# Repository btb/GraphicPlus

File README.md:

# GraphicPlus

Parallel printer card for Apple II

A clone of Orange Micro's Grappler+ printer card, from their published schematic, with the known bugfixes of their later revisions applied.

Component values not specified on the original schematic:

* C2, C4, C5, C5 - bypass capactors, 100nF should be fine.
* C1, C3, C7, C8 - on photos I've seen, C1 is 100pF, C3 is 470pF, C7 is 100pF. 100p for C8 should be fine as well.
* D1 - signal diode, 1n4148, 1n914, etc should be fine.

If you only want to use this as a firmware expansion card (i.e. for SoftSP), you can omit U5, U6, U10, U11, S1, D1, and J2.

Pins 2,4,6,8 of the port header are left unconnected for maximum compatibility with common PC parallel port IDC26F to DB25F dongles. If you need those pins to be connected to ground as in the original Grappler cards, short jumpers JP1,JP2,JP3,JP4.

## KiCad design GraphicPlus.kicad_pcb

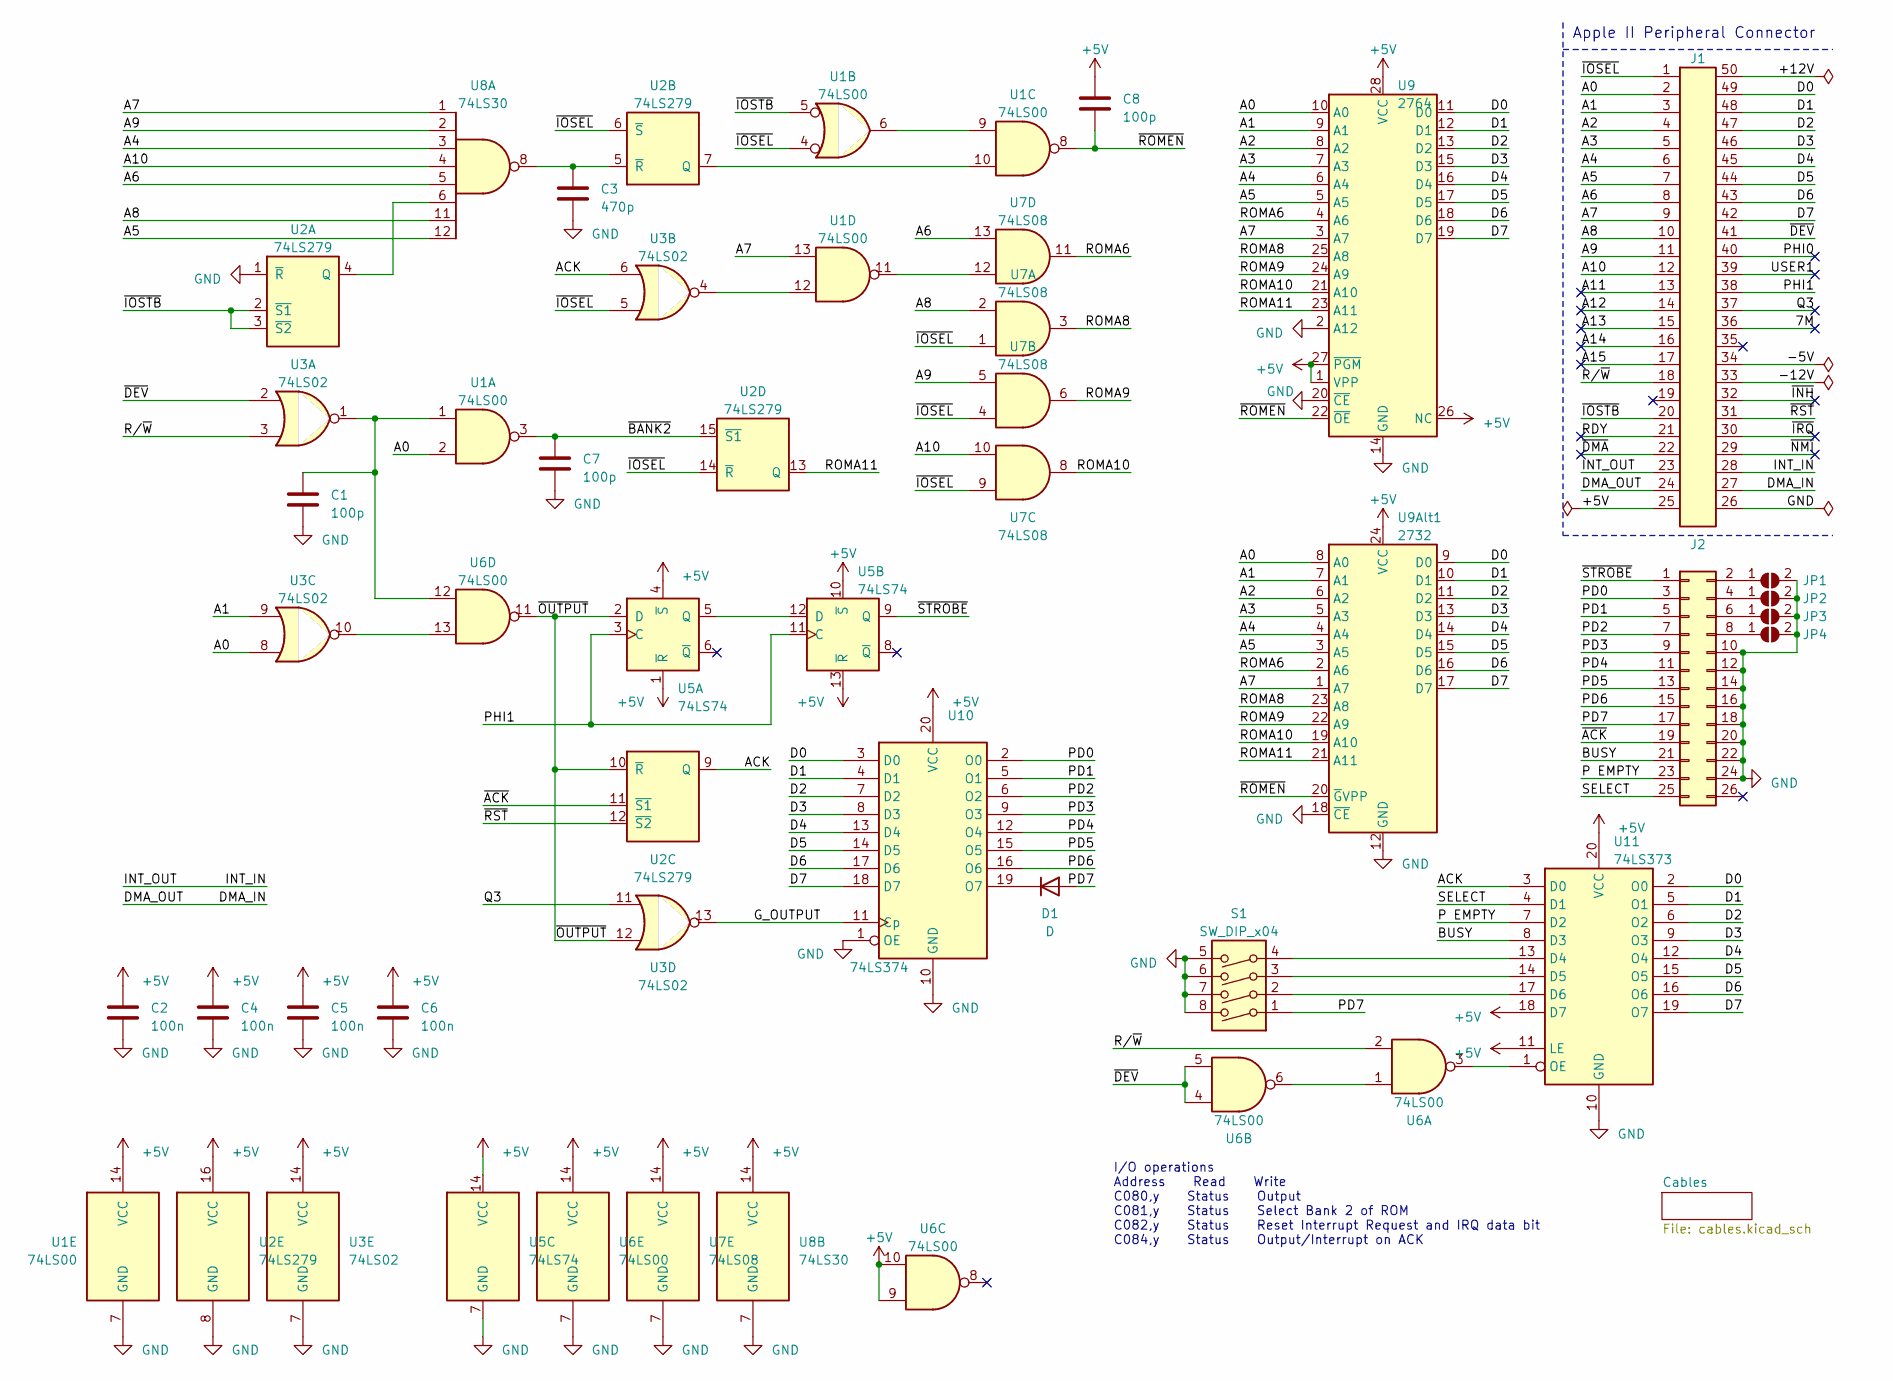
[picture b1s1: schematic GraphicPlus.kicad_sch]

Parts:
C1, C7, C8: 100p; C_Rect_L7.0mm_W2.0mm_P5.00mm
C2, C4, C5, C6: 100n; C_Rect_L7.0mm_W2.0mm_P5.00mm
C3: 470p; C_Rect_L7.0mm_W2.0mm_P5.00mm
D1: D; D_A-405_P7.62mm_Horizontal
J1: Apple II Expansion Bus; Apple II Expansion Edge Connector
J2: Printer Connector; PinHeader_2x13_P2.54mm_Horizontal
JP1, JP2, JP3, JP4: SolderJumper-2_P1.3mm_Open_RoundedPad1.0x1.5mm
S1: SW_DIP_x04; SW_DIP_SPSTx04_Slide_9.78x12.34mm_W7.62mm_P2.54mm
U1, U6: 74LS00; DIP-14_W7.62mm
U2: 74LS279; DIP-16_W7.62mm
U3: 74LS02; DIP-14_W7.62mm
U5: 74LS74; DIP-14_W7.62mm
U7: 74LS08; DIP-14_W7.62mm
U8: 74LS30; DIP-14_W7.62mm
U9: 2764; DIP-28_W15.24mm
U9Alt1: 2732; DIP-24_W15.24mm
U10: 74LS374; DIP-20_W7.62mm
U11: 74LS373; DIP-20_W7.62mm

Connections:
+5V: C2.1, C4.1, C5.1, C6.1, C8.1, J1.25 (+5V), U1.14 (VCC), U2.16 (VCC), U3.14 (VCC), U5.1 (~R), U5.4 (~S), U5.10 (~S), U5.13 (~R), U5.14 (VCC), U6.9, U6.10, U6.14 (VCC), U7.14 (VCC), U8.14 (VCC), U9.1 (VPP), U9.26 (NC), U9.27 (~PGM), U9.28 (VCC), U9Alt1.24 (VCC), U10.20 (VCC), U11.11 (LE), U11.18 (D7), U11.20 (VCC)
/7M: J1.36 (7M)
/+12V: J1.50 (-12V)
/-5V: J1.34 (-5V)
/-12V: J1.33 (-12V)
/A0: J1.2 (A00), U1.2, U3.8, U9.10 (A0), U9Alt1.8 (A0)
/A1: J1.3 (A01), U3.9, U9.9 (A1), U9Alt1.7 (A1)
/A2: J1.4 (A02), U9.8 (A2), U9Alt1.6 (A2)
/A3: J1.5 (A03), U9.7 (A3), U9Alt1.5 (A3)
/A4: J1.6 (A04), U8.3, U9.6 (A4), U9Alt1.4 (A4)
/A5: J1.7 (A05), U8.12, U9.5 (A5), U9Alt1.3 (A5)
/A6: J1.8 (A06), U7.13, U8.5
/A7: J1.9 (A07), U1.13, U8.1, U9.3 (A7), U9Alt1.1 (A7)
/A8: J1.10 (A08), U7.2, U8.11
/A9: J1.11 (A09), U7.5, U8.2
/A10: J1.12 (A10), U7.10, U8.4
/A11: J1.13 (A11)
/A12: J1.14 (A12)
/A13: J1.15 (A13)
/A14: J1.16 (A14)
/A15: J1.17 (A15)
/ACK: U2.9 (Q), U3.6, U11.3 (D0)
/BUSY: J2.21, U11.8 (D3)
/D0: J1.49 (D0), U9.11 (D0), U9Alt1.9 (D0), U10.3 (D0), U11.2 (O0)
/D1: J1.48 (D1), U9.12 (D1), U9Alt1.10 (D1), U10.4 (D1), U11.5 (O1)
/D2: J1.47 (D2), U9.13 (D2), U9Alt1.11 (D2), U10.7 (D2), U11.6 (O2)
/D3: J1.46 (D3), U9.15 (D3), U9Alt1.13 (D3), U10.8 (D3), U11.9 (O3)
/D4: J1.45 (D4), U9.16 (D4), U9Alt1.14 (D4), U10.13 (D4), U11.12 (O4)
/D5: J1.44 (D5), U9.17 (D5), U9Alt1.15 (D5), U10.14 (D5), U11.15 (O5)
/D6: J1.43 (D6), U9.18 (D6), U9Alt1.16 (D6), U10.17 (D6), U11.16 (O6)
/D7: J1.42 (D7), U9.19 (D7), U9Alt1.17 (D7), U10.18 (D7), U11.19 (O7)
/DMA_IN: J1.24 (DMA_OUT), J1.27 (DMA_IN)
/G_OUTPUT: U3.13, U10.11 (Cp)
/INT_IN: J1.23 (INT_OUT), J1.28 (INT_IN)
/P EMPTY: J2.23, U11.7 (D2)
/PD0: J2.3, U10.2 (O0)
/PD1: J2.5, U10.5 (O1)
/PD2: J2.7, U10.6 (O2)
/PD3: J2.9, U10.9 (O3)
/PD4: J2.11, U10.12 (O4)
/PD5: J2.13, U10.15 (O5)
/PD6: J2.15, U10.16 (O6)
/PD7: D1.2 (A), J2.17, S1.1
/PHI0: J1.40 (PHI0)
/PHI1: J1.38 (PHI1), U5.3 (C), U5.11 (C)
/Q3: J1.37 (Q3), U3.11
/RDY: J1.21 (RDY)
/ROMA6: U7.11, U9.4 (A6), U9Alt1.2 (A6)
/ROMA8: U7.3, U9.25 (A8), U9Alt1.23 (A8)
/ROMA9: U7.6, U9.24 (A9), U9Alt1.22 (A9)
/ROMA10: U7.8, U9.21 (A10), U9Alt1.19 (A10)
/ROMA11: U2.13 (Q), U9.23 (A11), U9Alt1.21 (A11)
/R/~W: J1.18 (R/~W), U3.3, U6.2
/SELECT: J2.25, U11.4 (D1)
/USER1: J1.39 (USER1)
/~ACK: J2.19, U2.11 (~S1)
/~BANK2: C7.1, U1.3, U2.15 (~S1)
/~DEV: J1.41 (~DEVICE_SELECT), U3.2, U6.4, U6.5
/~DMA: J1.22 (~DMA)
/~INH: J1.32 (~INH)
/~IOSEL: J1.1 (~IO_SELECT), U1.4, U2.6 (~S), U2.14 (~R), U3.5, U7.1, U7.4, U7.9
/~IOSTB: J1.20 (~I/O_STROBE), U1.5, U2.2 (~S1), U2.3 (~S2)
/~IRQ: J1.30 (~IRQ)
/~NMI: J1.29 (~NMI)
/~OUTPUT: U2.10 (~R), U3.12, U5.2 (D), U6.11
/~ROMEN: C8.2, U1.8, U9.22 (~OE), U9Alt1.20 (~GVPP)
/~RST: J1.31 (~RES), U2.12 (~S2)
/~STROBE: J2.1, U5.9 (Q)
GND: C1.2, C2.2, C3.2, C4.2, C5.2, C6.2, C7.2, J1.26 (GND), J2.10, J2.12, J2.14, J2.16, J2.18, J2.20, J2.22, J2.24, JP1.2 (B), JP2.2 (B), JP3.2 (B), JP4.2 (B), S1.5, S1.6, S1.7, S1.8, U1.7 (GND), U2.1 (~R), U2.8 (GND), U3.7 (GND), U5.7 (GND), U6.7 (GND), U7.7 (GND), U8.7 (GND), U9.2 (A12), U9.14 (GND), U9.20 (~CE), U9Alt1.12 (GND), U9Alt1.18 (~CE), U10.1 (OE), U10.10 (GND), U11.10 (GND)
unnamed: C1.1, U1.1, U3.1, U6.12
unnamed: D1.1 (K), U10.19 (O7)
unnamed: J2.2, JP1.1 (A)
unnamed: J2.4, JP2.1 (A)
unnamed: J2.6, JP3.1 (A)
unnamed: J2.8, JP4.1 (A)
unnamed: U1.6, U1.9
unnamed: U1.11, U7.12
unnamed: U1.12, U3.4
unnamed: U2.4 (Q), U8.6
unnamed: U1.10, U2.7 (Q)
unnamed: C3.1, U2.5 (~R), U8.8
unnamed: U3.10, U6.13
unnamed: U5.5 (Q), U5.12 (D)
unnamed: U6.1, U6.6
unnamed: S1.4, U11.13 (D4)
unnamed: S1.3, U11.14 (D5)
unnamed: S1.2, U11.17 (D6)
unnamed: U6.3, U11.1 (OE)

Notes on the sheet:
Apple II Peripheral Connector
I/O operations Address Read Write C080,y Status Output C081,y Status Select Bank 2 of ROM C082,y Status Reset Interrupt Request and IRQ data bit C084,y Status Output/Interrupt on ACK

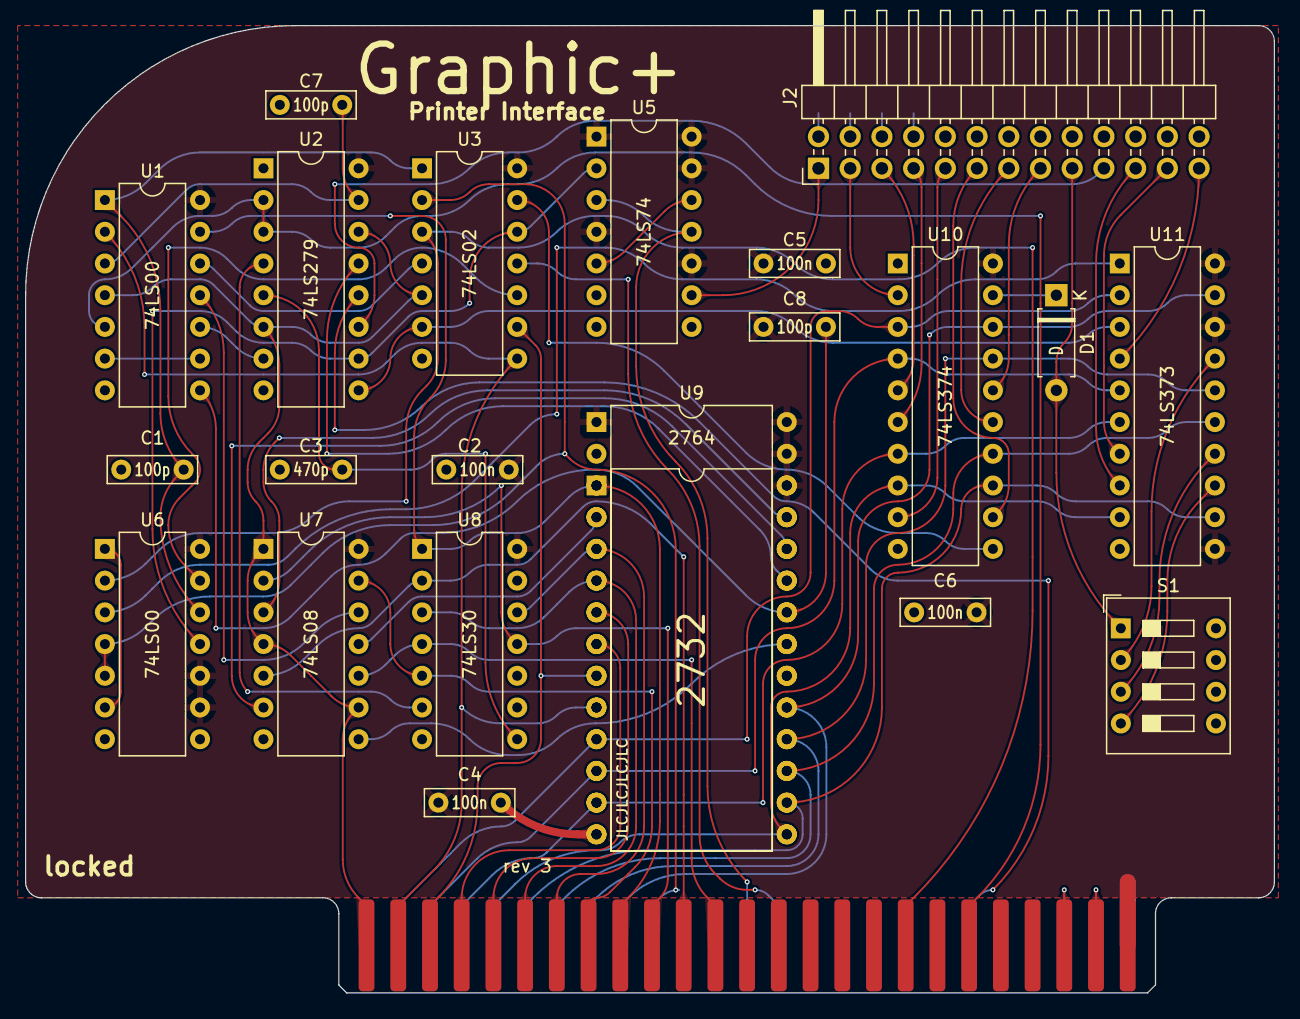
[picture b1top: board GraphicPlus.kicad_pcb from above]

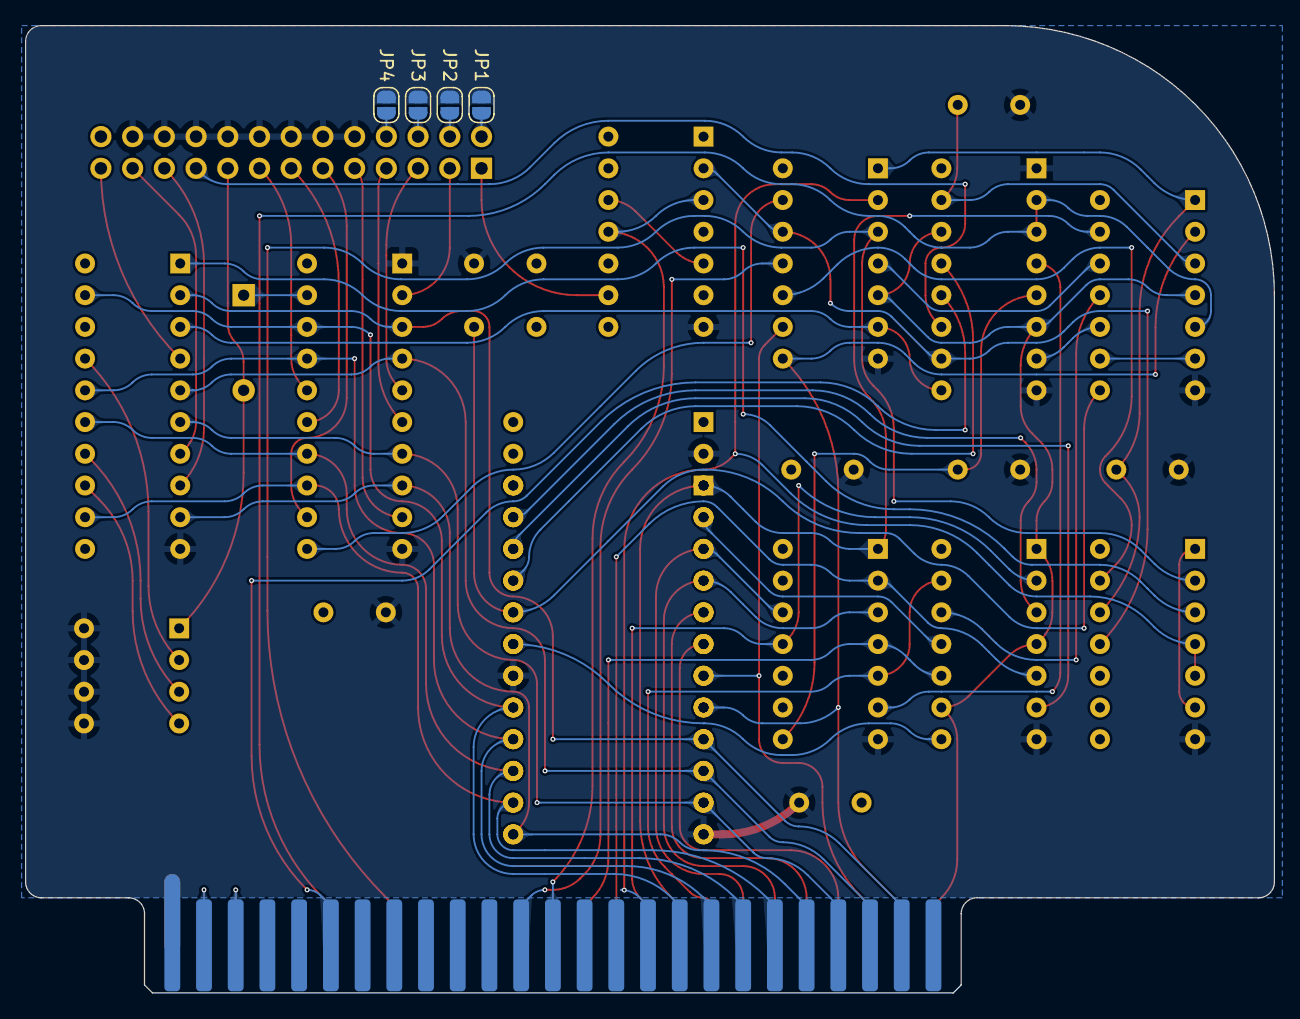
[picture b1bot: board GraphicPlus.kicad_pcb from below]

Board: 2 copper layers, 100.0 x 77.5 mm, 27 parts (4 on the bottom side), 72 nets.

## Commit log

2023-09-29 add kicad project
2023-09-29 native 374 version
2023-09-29 finish up rev 1
2023-09-29 add files
2023-09-29 rev 2, PC dongle compatibility
2023-09-29 consolidate 74ls00 chips, better spacing
2023-09-29 SW1->S1
2023-10-01 fix order number size
2023-10-01 let power on pin 26 of DIP28 EPROM
2023-10-01 U2 pin 1 supposed to be GND, not +5
2023-10-01 Delete gerbers.zip
    rev2 defective
2023-10-01 force +5 on U9alt pin 26
2023-10-01 rev3 fixes
